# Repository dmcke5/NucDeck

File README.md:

# NucDeck
The Open Source DIY Handheld Gaming PC!

Refer to "NucDeck Assembly Instructions.PDF" for mechanical assembly details. Information for the electronics will be added once the controller PCB's are complete.

There are two different versions of the housing, Standard and NoRGB. The NoRGB version has had
the RGB joystick surrounds removed to simplify printing. If you choose the NoRGB version you can leave all of the 
associated components off the PCB's to save on cost.

There are two different versions of the buttons, membrane and clicky. The Membrane buttons are shorter and are
designed to be used with silicone membranes. I've included files for molds to make the membranes. If you have a resin printer
I encourage you to give this a try as it improves the feel of the buttons dramatically. FDM printers will struggle to produce the accuracy required to make these parts. The clicky version is slightly taller and can be used without the membranes.

Total Cost of parts approximately: $311 USD

This is based on PCBway's pricing for the PCB's and is not including a NUC or any shipping charges. I've probably missed counting something so I would budget for a little more!

Here's a breakdown of the costs:
- Digikey parts: $55 USD
- PCB's (Set of 5 due to MOQ): $204 USD
- Aliexpress Parts: $52 USD

If you can organise a group of 5 people who want a set of PCB's, you will greatly reduce your total cost to build.

#### Project Status
- [x] 3D Files
- [x] Software: V1.0 ready for testing. Motion controls not yet implemented
- [x] PCBs: Complete

Watch the series on Youtube as I design, build and test parts of this project:
- [Episode 1](https://youtu.be/xVYYCx3Qt4Y)
- [Episode 2](https://youtu.be/nOXd3axX4fw)
- [Episode 3](https://youtu.be/yHMnScoKIOE)
- [Episode 4](https://youtu.be/rP_sMztufNs)
- [Episode 5](https://youtu.be/sQocfy4pwIQ)
- [Bonus Episode - Battery Life Testing](https://youtu.be/6FQKwnMxRxI)
- [Episode 6](https://youtu.be/mfuAvgmuT2s)
- [Episode 7](https://youtu.be/nFNw7_WkteA)
- [Episode 8](https://youtu.be/YYRD0Zlga5s)
- [Episode 9](https://youtu.be/t9Rao_BeIeM)

I've found links for all of the parts on Aliexpress since its probably the cheapest option and will ship worldwide.

## Parts List

#### Display

Any 1024x600 50 Pin RGB Panel with overall dimensions no greater than 164.9x100x3.3mm.
This is the 700nit IPS panel I ended up using: https://www.aliexpress.com/item/1005005315348504.html

#### Display Driver

Pick the "PCB800812V1" option:
https://www.aliexpress.com/item/1005004252996145.html

#### USB Touch Controller

Pick option "USB Controller":
https://www.aliexpress.com/item/32976239800.html

#### Capacitive Touch Panel

This is the seller I used, but anyone selling for the same model tablet (Pritom K7) should do:
https://www.aliexpress.com/item/1005002490383977.html

#### Joysticks

Joysticks are an Alps RKJX21224001. Here's a cheap seller on aliexpress:
https://www.aliexpress.com/item/1005005264696228.html
Joystick caps are Xbox One compatible.

#### Batteries

4x 605080 3000mah Lithium cells. Here's a cheap supplier on Aliexpress:
https://www.aliexpress.com/item/32990176071.html

#### Info Screen

0.96" IPS 80x160 ST7735 TFT Display

You need the one these guys refer to as "Spliced Type".
https://www.aliexpress.com/item/1005001598020071.html

#### Threaded Inserts

Measurments are: Thread x OD x Length

17x M2x3.2x4

10x M3x5x5

2x M3x5x4

https://www.aliexpress.com/item/1005003582355741.html

#### Standoffs

10x M2x6mm Male to Female Standoffs
https://www.aliexpress.com/item/4001271908929.html

#### Trigger Springs

--NOTE-- Ignore the wire thickness in the Assembly Drawing, it is incorrect. I will fix it when I next need to make changes. Correct thickness listed here.
These guys have a lot of different options, they are pretty cheap so I'd grab a few different wire thicknesses
and test them out to see what you like. You need about 2mm ID on the coil section, so look for an ID of at least double the wire
thickness greater than 2mm. I found 0.4mm to feel a bit too thin, and 0.7mm is about the limit of the trigger supports so 0.5-0.6mm is probably the sweet spot.
https://www.aliexpress.com/item/1005004968066601.html

#### Trigger Magnets

You'll never need fridge magnets again!
https://www.aliexpress.com/item/1005003794726533.html

#### RGB Lights

You'll need both RGB LED's and WS2811 IC's if you're adding RGB to your controller PCB's.
These are the LED's I used. Any alternative in the same sized package should be fine too, just be cautious of
differing pin configurations.
https://www.aliexpress.com/item/1005003719602946.html

WS2811 IC's:
https://www.aliexpress.com/item/32844615804.html

#### Screws

Here's a list of the screws required for assembly. This list is also in the assembly instructions. SCHS is just a standard allen key head screw. CSK is a countersunk head screw. Most bolt suppliers should have these, otherwise ebay or aliexpress is your friend.

12x M3x6mm SHCS
2x M2x16 CSK
9x M2x5 CSK
14x M2x4 SHCS

#### 4s Cell Balancer
https://www.aliexpress.com/item/1005005827876691.html

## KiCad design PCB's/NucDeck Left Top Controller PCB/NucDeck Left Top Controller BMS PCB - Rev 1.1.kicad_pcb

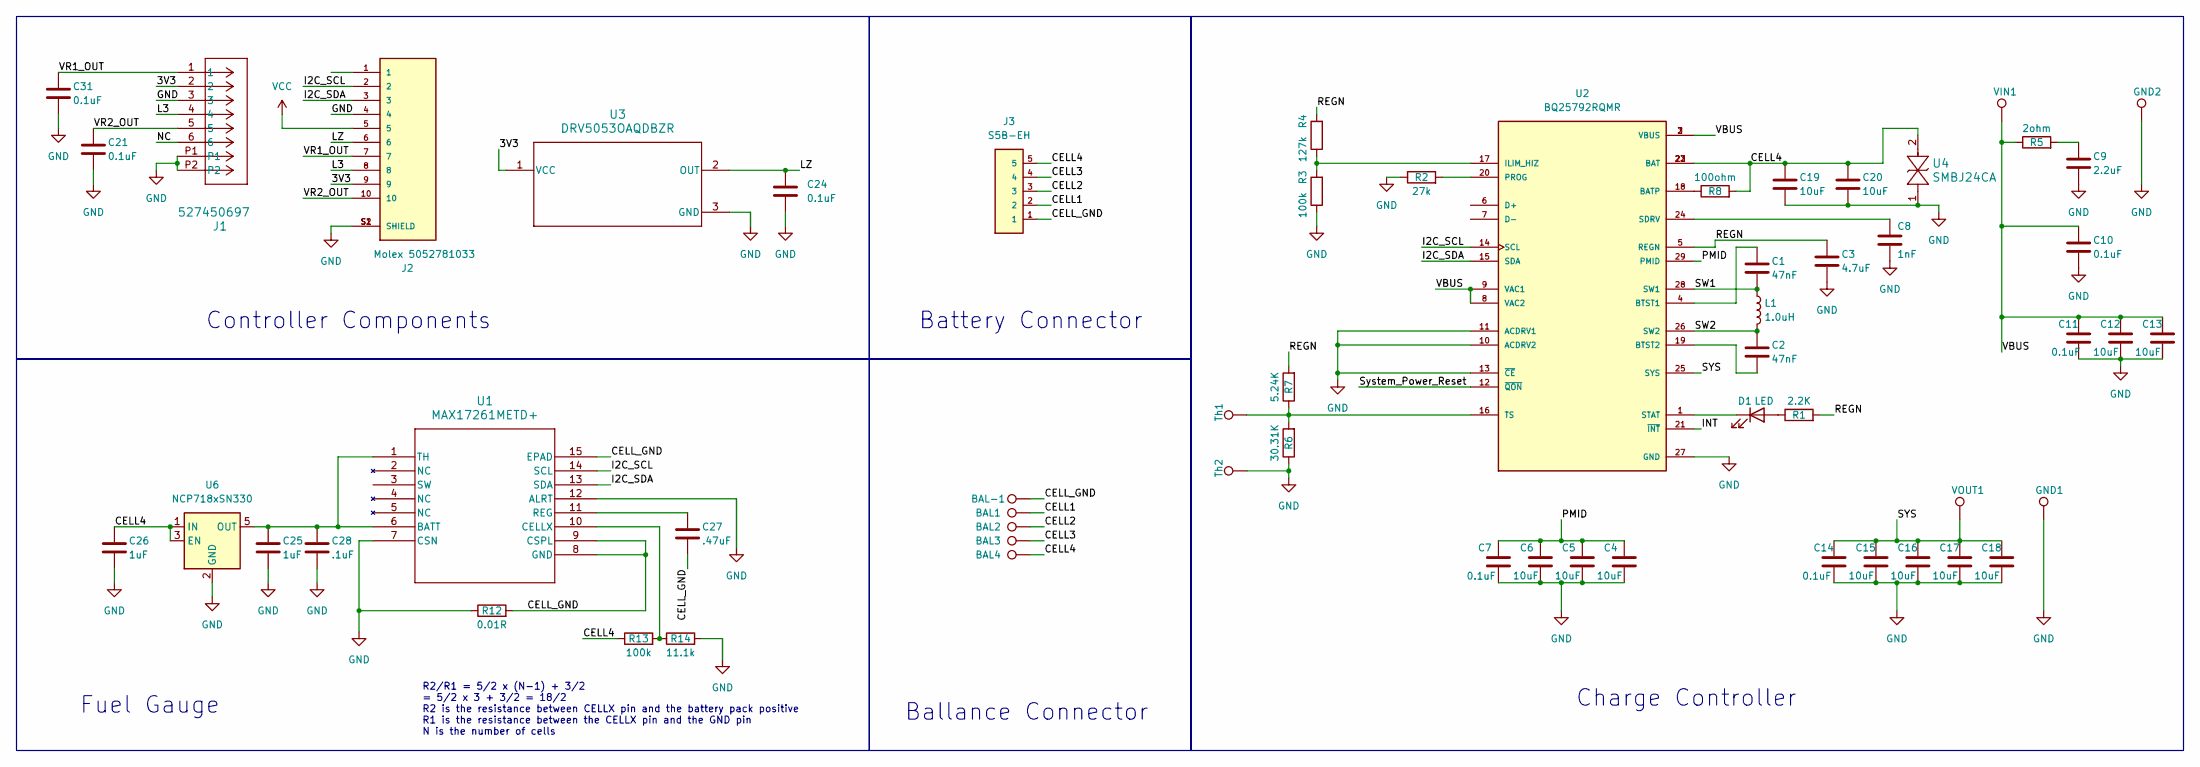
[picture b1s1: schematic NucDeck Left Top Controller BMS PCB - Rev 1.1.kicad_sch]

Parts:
BAL1, BAL2, BAL3, BAL4: TestPoint; TestPoint_Pad_1.0x1.0mm
BAL-1: TestPoint; TestPoint_Pad_1.0x1.0mm
C1, C2: 47nF; C_0603_1608Metric
C3: 4.7uF; C_0603_1608Metric
C4, C5, C6, C12, C13, C15, C16, C17, C18: 10uF; C_0805_2012Metric
C7, C10, C11, C14, C21, C24, C31: 0.1uF; C_0603_1608Metric
C8: 1nF; C_0603_1608Metric
C9: 2.2uF; C_0603_1608Metric
C19, C20: 10uF; C_0603_1608Metric
C25, C26: 1uF; C_0603_1608Metric
C27: .47uF; C_0603_1608Metric
C28: .1uF; C_0603_1608Metric
D1: LED; LED_0603_1608Metric
GND1, GND2: TestPoint; TestPoint_THTPad_D2.0mm_Drill1.0mm
J1: 527450697; CON_527450697_MOL
J2: Molex 5052781033; PARTREV A
J3: S5B-EH; JST_EH_S5B-EH_1x05_P2.50mm_Horizontal
L1: 1.0uH; IND_SPM6530_TDK
R1: 2.2K; R_0603_1608Metric
R2: 27k; R_0603_1608Metric
R3, R13: 100k; R_0603_1608Metric
R4: 127k; R_0603_1608Metric
R5: 2ohm; R_0603_1608Metric
R6: 30.31K; R_0603_1608Metric
R7: 5.24K; R_0603_1608Metric
R8: 100ohm; R_0603_1608Metric
R12: 0.01R; R_2512_6332Metric
R14: 11.1k; R_0603_1608Metric
Th1, Th2: 10K; TestPoint_THTPad_D1.0mm_Drill0.5mm
U1: MAX17261METD+; 21-0137_T1433+2C_MXM
U2: BQ25792RQMR; QFN40P400X400X100-29N; PARTREV 11/2019
U3: DRV5053OAQDBZR; DBZ0003A_N
U4: SMBJ24CA; SMBJ24CA_LTF
U6: NCP718xSN330; SOT-23-5
VIN1: TestPoint; TestPoint_THTPad_D2.0mm_Drill1.0mm
VOUT1: TestPoint; TestPoint_THTPad_D2.0mm_Drill1.0mm

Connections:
/3V3: J1.2, J2.9, U3.1 (VCC)
/CELL1: BAL1.1, J3.2
/CELL2: BAL2.1, J3.3
/CELL3: BAL3.1, J3.4
/CELL4: BAL4.1, C19.1, C20.1, C26.1, J3.5, R8.2, R13.1, U2.22 (BAT), U2.23 (BAT), U4.2, U6.1 (IN), U6.3 (EN)
/CELL_GND: BAL-1.1, C27.2, J3.1, R12.2, U1.8 (GND), U1.9 (CSPL), U1.15 (EPAD)
/I2C_SCL: J2.2, U1.14 (SCL), U2.14 (SCL)
/I2C_SDA: J2.3, U1.13 (SDA), U2.15 (SDA)
/INT: U2.21 (~INT)
/L3: J1.4, J2.8
/LZ: C24.1, J2.6, U3.2 (OUT)
/NC: J1.6
/PMID: C4.1, C5.1, C6.1, C7.1, U2.29 (PMID)
/REGN: C3.1, R1.2, R4.2, R7.2, U2.5 (REGN)
/SW1: C1.2, L1.1, U2.28 (SW1)
/SW2: C2.1, L1.2, U2.26 (SW2)
/SYS: C14.1, C15.1, C16.1, C17.1, C18.1, U2.25 (SYS), VOUT1.1; also elsewhere on the board
/System_Power_Reset: U2.12 (~QON)
/VBUS: C10.1, C11.1, C12.1, C13.1, R5.1, U2.2 (VBUS), U2.3 (VBUS), U2.8 (VAC2), U2.9 (VAC1), VIN1.1; also elsewhere on the board
/VR1_OUT: C31.1, J1.1, J2.7
/VR2_OUT: C21.1, J1.5, J2.10
GND: C3.2, C4.2, C5.2, C6.2, C7.2, C8.2, C9.2, C10.2, C11.2, C12.2, C13.2, C14.2, C15.2, C16.2, C17.2, C18.2, C19.2, C20.2, C21.2, C24.2, C25.2, C26.2, C28.2, C31.2, GND1.1, GND2.1, J1.3, J1.P1, J1.P2, J2.4, J2.11, J2.12, J2.S1 (SHIELD), J2.S2 (SHIELD), R2.1, R3.1, R6.1, R12.1, R14.2, Th2.1, U1.7 (CSN), U1.12 (ALRT), U2.10 (ACDRV2), U2.11 (ACDRV1), U2.13 (~CE), U2.27 (GND), U3.3 (GND), U4.1, U6.2 (GND); also elsewhere on the board
unnamed: C9.1, R5.2
unnamed: D1.2 (A), R1.1
unnamed: D1.1 (K), U2.1 (STAT)
unnamed: C25.1, C28.1, U1.1 (TH), U1.6 (BATT), U6.5 (OUT)
unnamed: R13.2, R14.1, U1.10 (CELLX)
unnamed: C27.1, U1.11 (REG)
unnamed: R8.1, U2.18 (BATP)
unnamed: C1.1, U2.4 (BTST1)
unnamed: C2.2, U2.19 (BTST2)
unnamed: R3.2, R4.1, U2.17 (ILIM_HIZ)
unnamed: R2.2, U2.20 (PROG)
unnamed: C8.1, U2.24 (SDRV)
unnamed: R6.2, R7.1, Th1.1, U2.16 (TS)
VCC: J2.5

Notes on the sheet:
Ballance Connector
Controller Components
Fuel Gauge
R2/R1 = 5/2 x (N-1) + 3/2 = 5/2 x 3 + 3/2 = 18/2 R2 is the resistance between CELLX pin and the battery pack positive R1 is the resistance between the CELLX pin and the GND pin N is the number of cells
Battery Connector
Charge Controller

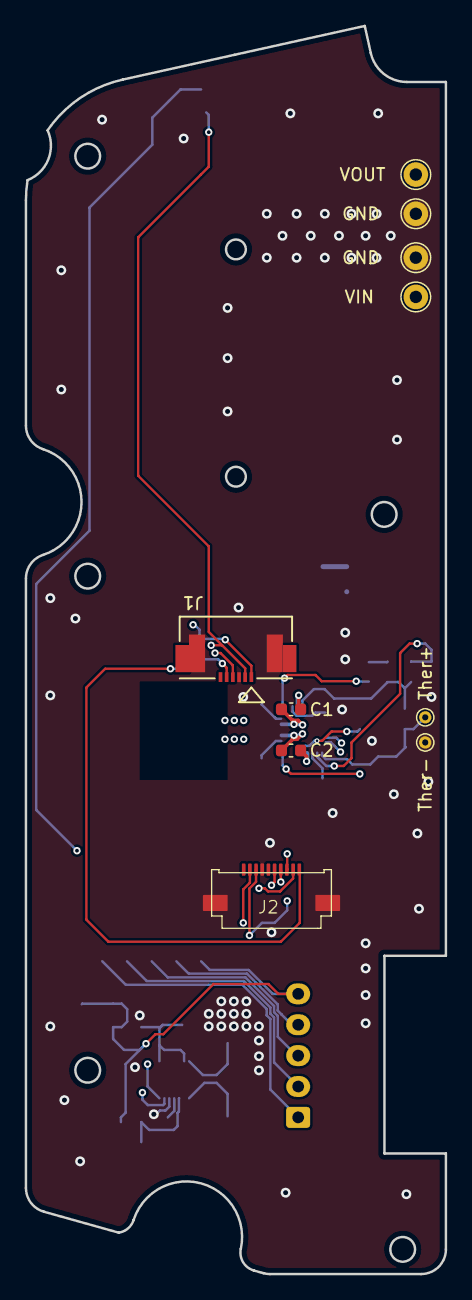
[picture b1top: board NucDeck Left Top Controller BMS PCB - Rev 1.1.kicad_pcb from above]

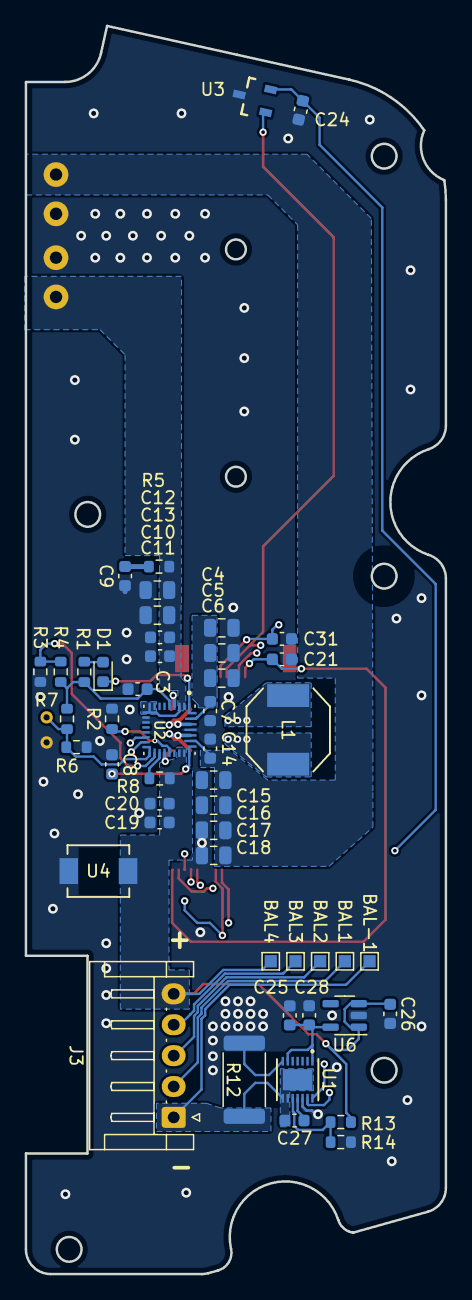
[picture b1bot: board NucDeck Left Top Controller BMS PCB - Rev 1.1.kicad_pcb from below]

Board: 4 copper layers, 34.0 x 101.0 mm, 59 parts (49 on the bottom side), 32 nets.

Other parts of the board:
GND: TestPoint; TestPoint_THTPad_D2.0mm_Drill1.0mm
GND#2: TestPoint; TestPoint_THTPad_D2.0mm_Drill1.0mm
VIN: TestPoint; TestPoint_THTPad_D2.0mm_Drill1.0mm
VOUT: TestPoint; TestPoint_THTPad_D2.0mm_Drill1.0mm

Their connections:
/SYS: VOUT.1; also elsewhere on the board
/VBUS: VIN.1; also elsewhere on the board
GND: GND.1, GND#2.1; also elsewhere on the board

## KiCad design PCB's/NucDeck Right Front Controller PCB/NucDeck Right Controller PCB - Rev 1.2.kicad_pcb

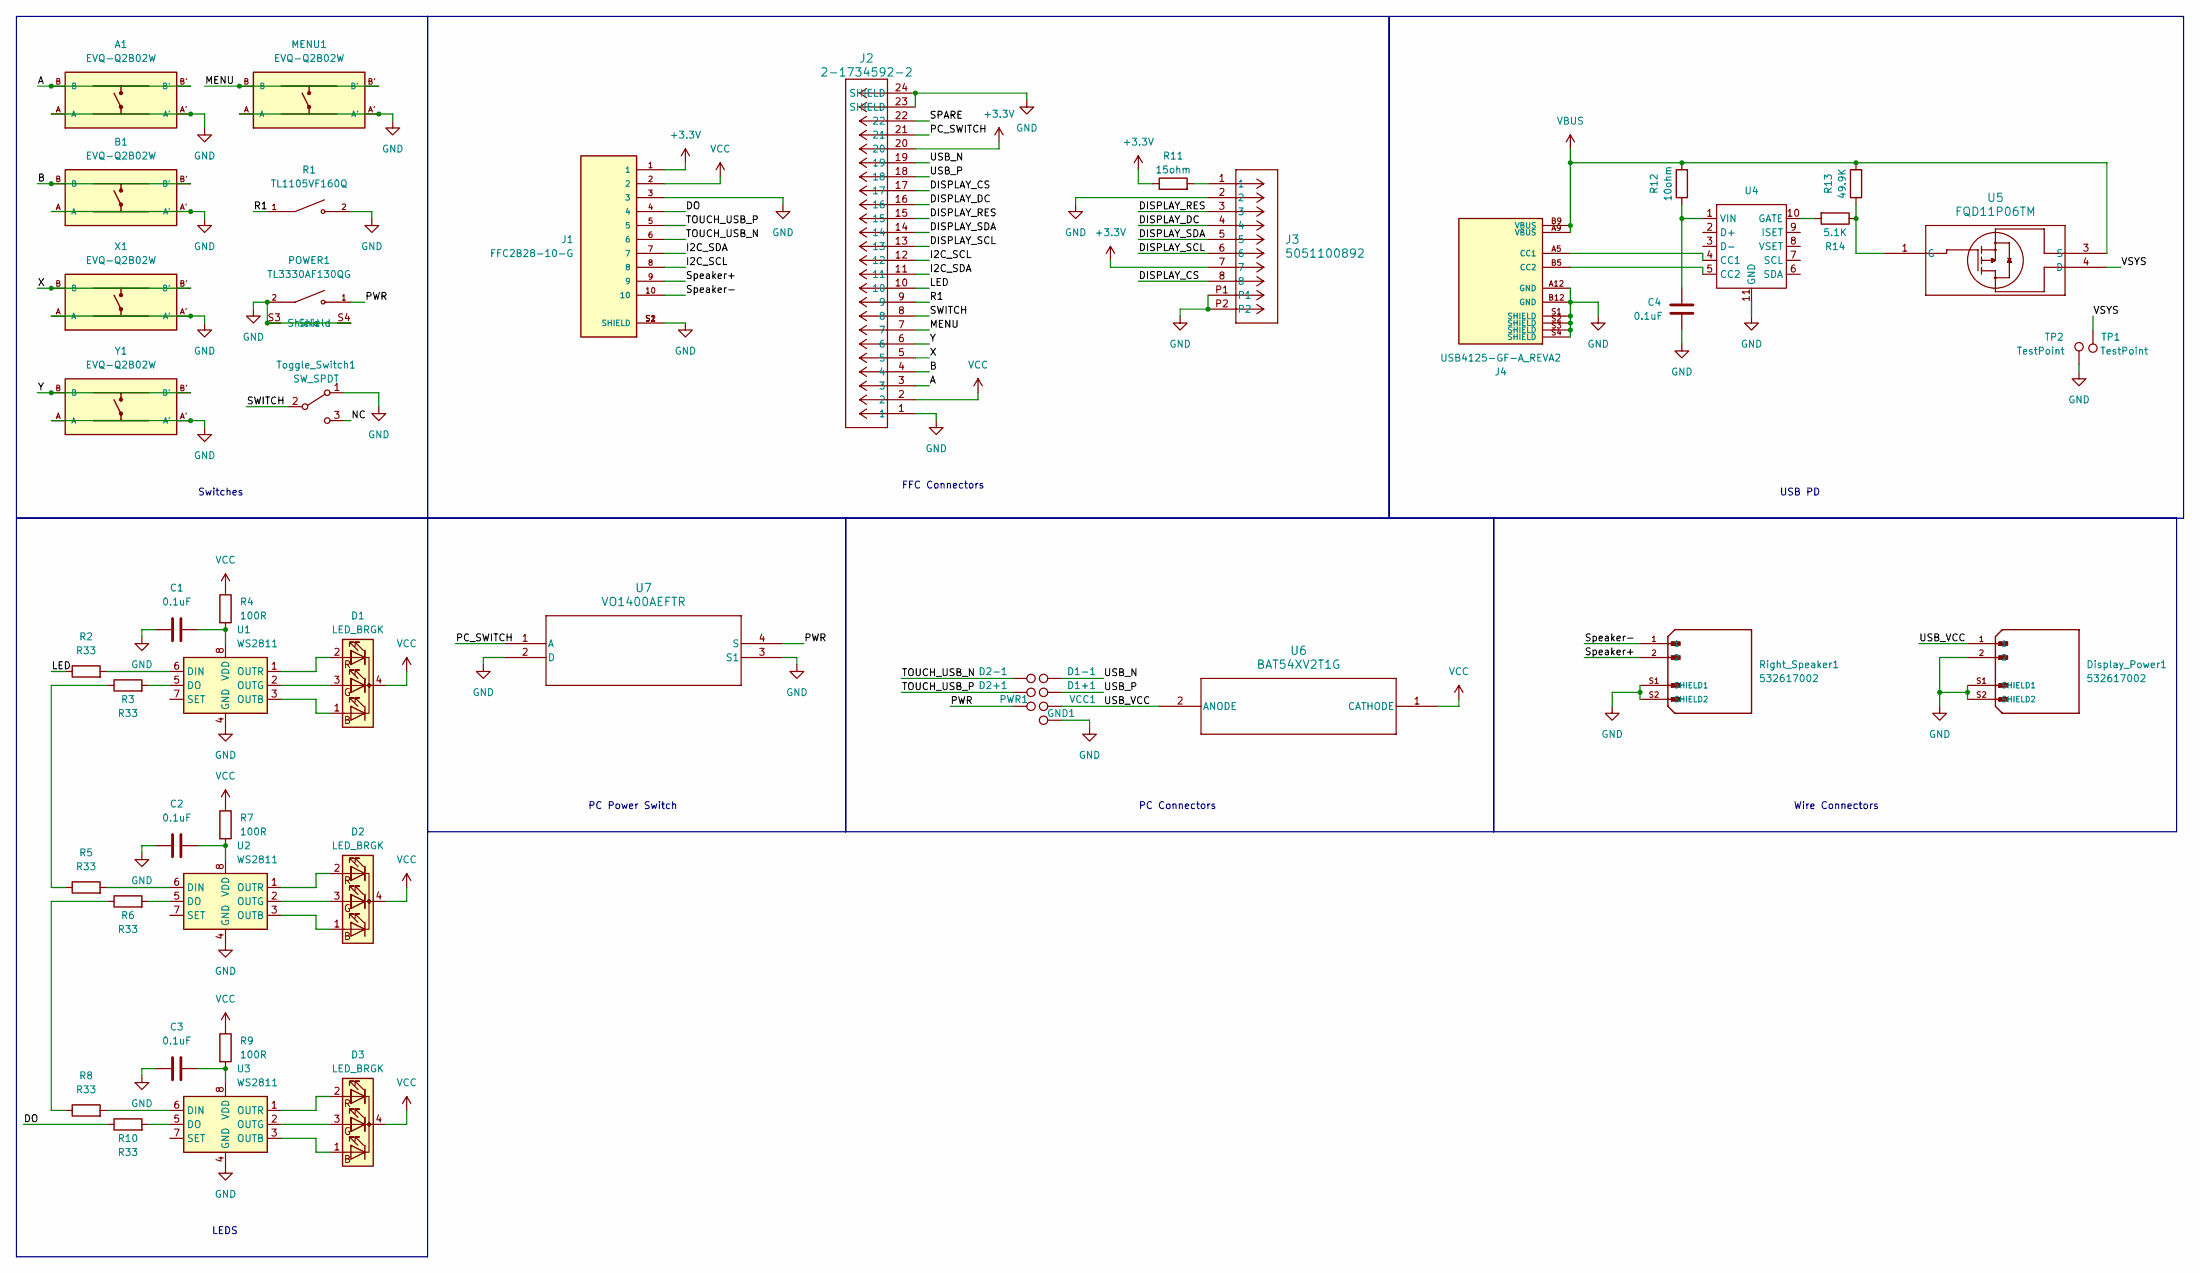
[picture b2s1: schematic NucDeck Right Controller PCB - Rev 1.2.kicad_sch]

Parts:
A1: EVQ-Q2B02W; SW_EVQ-Q2B02W
B1: EVQ-Q2B02W; SW_EVQ-Q2B02W
C1, C2, C3, C4: 0.1uF; C_0603_1608Metric_Pad1.08x0.95mm_HandSolder
D1, D2, D3: LED_BRGK; LED_T36K3BGR-05D000121U1930
D1+1, D1-1, D2+1, D2-1: TestPoint; TestPoint_THTPad_D1.0mm_Drill0.5mm
Display_Power1: 532617002; MOLEX_532617002; PARTREV B; DigiKey_Part_Number WM25389TR-ND
GND1: TestPoint; TestPoint_THTPad_D1.0mm_Drill0.5mm
J1: FFC2B28-10-G; Molex 5052781033; PARTREV A
J2: 2-1734592-2; CONN22_2-1734592-2
J3: 5051100892; CON_5051100892_MOL
J4: USB4125-GF-A_REVA2; GCT_USB4125-GF-A_REVA2; PARTREV Rev A2; DigiKey_Part_Number 2073-USB4125-GF-ATR-ND
MENU1: EVQ-Q2B02W; SW_EVQ-Q2B02W
POWER1: TL3330AF130QG; SW_TL3330AF130QG; PARTREV B
PWR1: TestPoint; TestPoint_THTPad_D1.0mm_Drill0.5mm
R1: TL1105VF160Q; SW_TL1105VF160Q; PARTREV C
R2, R3, R5, R6, R8, R10: R33; R_0603_1608Metric_Pad0.98x0.95mm_HandSolder
R4, R7, R9: 100R; R_0603_1608Metric_Pad0.98x0.95mm_HandSolder
R11: 15ohm; R_0603_1608Metric_Pad0.98x0.95mm_HandSolder
R12: 10ohm; R_0603_1608Metric_Pad0.98x0.95mm_HandSolder
R13: 49.9K; R_0603_1608Metric_Pad0.98x0.95mm_HandSolder
R14: 5.1K; R_0603_1608Metric_Pad0.98x0.95mm_HandSolder
Right_Speaker1: 532617002; MOLEX_532617002; PARTREV B; DigiKey_Part_Number WM25389TR-ND
TP1, TP2: TestPoint; TestPoint_THTPad_D1.5mm_Drill0.7mm
Toggle_Switch1: SW_SPDT; NKK SS12SBP2
U1, U2, U3: WS2811; SOP-8_3.9x4.9mm_P1.27mm
U4: DFN-10-1EP_3x3mm_P0.5mm_EP1.7x2.5mm
U5: FQD11P06TM; TO-252-3_ONS
U6: BAT54XV2T1G; SOD-523_0P9X1P3_ONS
U7: VO1400AEFTR; SO-4_VO_VIS
VCC1: TestPoint; TestPoint_THTPad_D1.0mm_Drill0.5mm
X1: EVQ-Q2B02W; SW_EVQ-Q2B02W
Y1: EVQ-Q2B02W; SW_EVQ-Q2B02W

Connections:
+3.3V: J1.1, J2.20, J3.7, R11.1
/A: A1.B, A1.B', J2.3
/B: B1.B, B1.B', J2.4
/DISPLAY_CS: J2.17, J3.8
/DISPLAY_DC: J2.16, J3.4
/DISPLAY_RES: J2.15, J3.3
/DISPLAY_SCL: J2.13, J3.6
/DISPLAY_SDA: J2.14, J3.5
/DO: J1.4, R10.1
/I2C_SCL: J1.8, J2.12
/I2C_SDA: J1.7, J2.11
/LED: J2.10, R2.1
/MENU: J2.7, MENU1.B, MENU1.B'
/NC: Toggle_Switch1.3 (C)
/PC_SWITCH: J2.21, U7.1 (A)
/PWR: POWER1.1, PWR1.1, U7.4 (S)
/R1: J2.9, R1.1
/SPARE: J2.22
/SWITCH: J2.8, Toggle_Switch1.2 (B)
/Speaker+: J1.9, Right_Speaker1.2
/Speaker-: J1.10, Right_Speaker1.1
/TOUCH_USB_N: D2-1.1, J1.6
/TOUCH_USB_P: D2+1.1, J1.5
/USB_N: D1-1.1, J2.19
/USB_P: D1+1.1, J2.18
/USB_VCC: Display_Power1.1, U6.2 (ANODE), VCC1.1
/VSYS: TP1.1, U5.4 (D)
/X: J2.5, X1.B, X1.B'
/Y: J2.6, Y1.B, Y1.B'
GND: A1.A, A1.A', B1.A, B1.A', C1.1, C2.1, C3.1, C4.2, Display_Power1.2, Display_Power1.S1 (SHIELD1), Display_Power1.S2 (SHIELD2), GND1.1, J1.3, J1.11, J1.12, J1.S1 (SHIELD), J1.S2 (SHIELD), J2.1, J2.23 (SHIELD), J2.24 (SHIELD), J3.2, J3.P1, J3.P2, J4.1, J4.2, J4.3, J4.4, J4.A12 (GND), J4.B12 (GND), J4.S1 (SHIELD), J4.S2 (SHIELD), J4.S3 (SHIELD), J4.S4 (SHIELD), MENU1.A, MENU1.A', POWER1.2, POWER1.S1, POWER1.S3 (Shield), POWER1.S4 (Shield), R1.2, R1.S1, R1.S2, Right_Speaker1.S1 (SHIELD1), Right_Speaker1.S2 (SHIELD2), TP2.1, Toggle_Switch1.1 (A), U1.4 (GND), U2.4 (GND), U3.4 (GND), U4.11 (GND), U7.2 (D), U7.3 (S1), X1.A, X1.A', Y1.A, Y1.A'
unnamed: D1.1 (BA), U1.3 (OUTB)
unnamed: D1.3 (GA), U1.2 (OUTG)
unnamed: D1.2 (RA), U1.1 (OUTR)
unnamed: D2.1 (BA), U2.3 (OUTB)
unnamed: D2.3 (GA), U2.2 (OUTG)
unnamed: D2.2 (RA), U2.1 (OUTR)
unnamed: D3.1 (BA), U3.3 (OUTB)
unnamed: D3.3 (GA), U3.2 (OUTG)
unnamed: D3.2 (RA), U3.1 (OUTR)
unnamed: J3.1, R11.2
unnamed: J4.A5 (CC1), U4.4 (CC1)
unnamed: J4.B5 (CC2), U4.5 (CC2)
unnamed: R3.1, R5.1
unnamed: R6.1, R8.1
unnamed: R2.2, U1.6 (DIN)
unnamed: R3.2, U1.5 (DO)
unnamed: C1.2, R4.2, U1.8 (VDD)
unnamed: R5.2, U2.6 (DIN)
unnamed: R6.2, U2.5 (DO)
unnamed: C2.2, R7.2, U2.8 (VDD)
unnamed: R8.2, U3.6 (DIN)
unnamed: R10.2, U3.5 (DO)
unnamed: C3.2, R9.2, U3.8 (VDD)
unnamed: R14.2, U4.10 (GATE)
unnamed: C4.1, R12.1, U4.1 (VIN)
unnamed: R13.1, R14.1, U5.1 (G)
VBUS: J4.A9 (VBUS), J4.B9 (VBUS), R12.2, R13.2, U5.3 (S)
VCC: D1.4 (K), D2.4 (K), D3.4 (K), J1.2, J2.2, R4.1, R7.1, R9.1, U6.1 (CATHODE)

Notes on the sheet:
Switches
PC Power Switch
PC Connectors
FFC Connectors
LEDS
USB PD
Wire Connectors

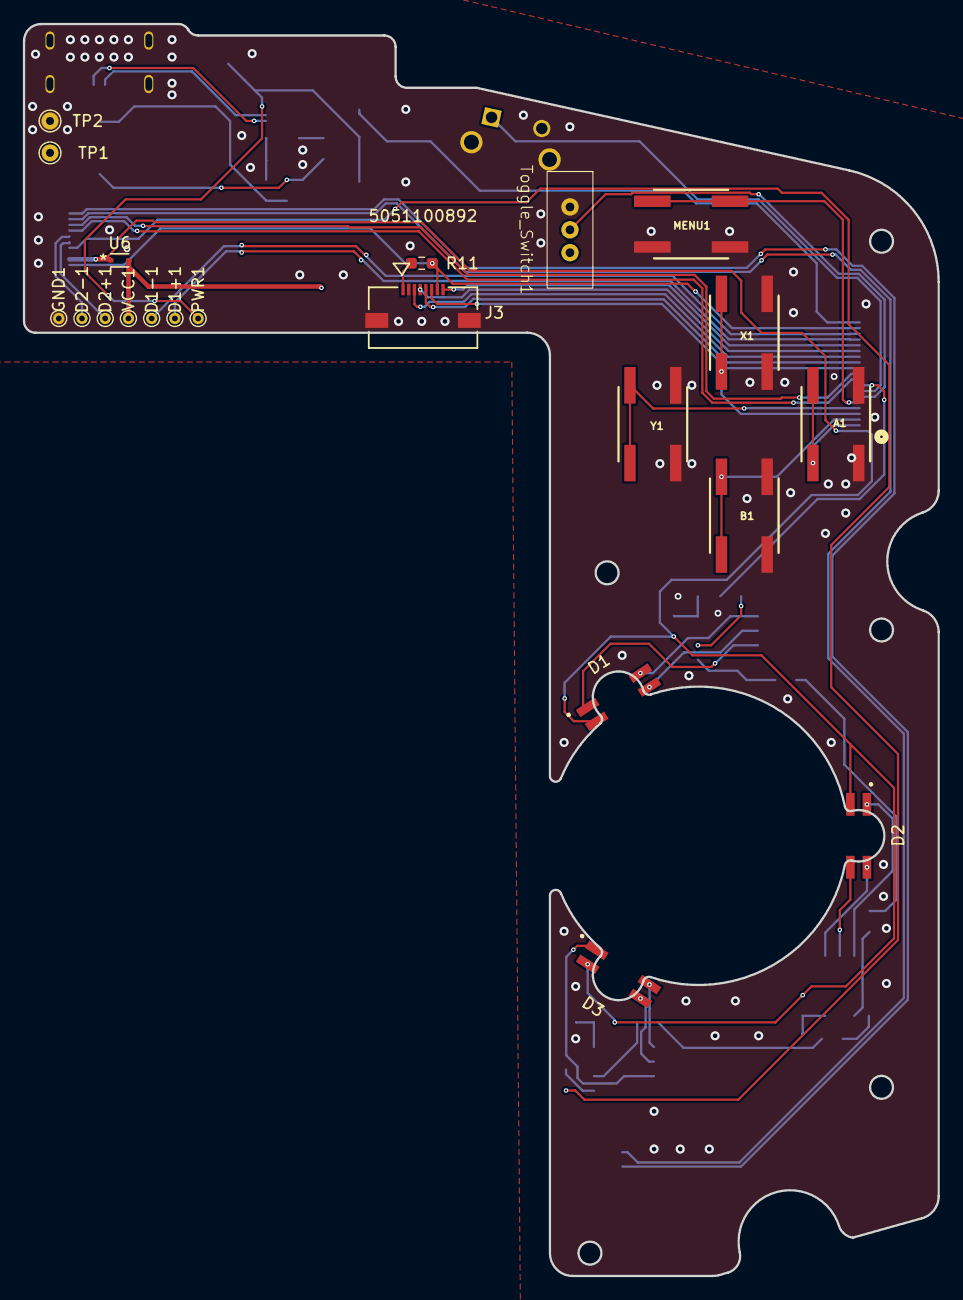
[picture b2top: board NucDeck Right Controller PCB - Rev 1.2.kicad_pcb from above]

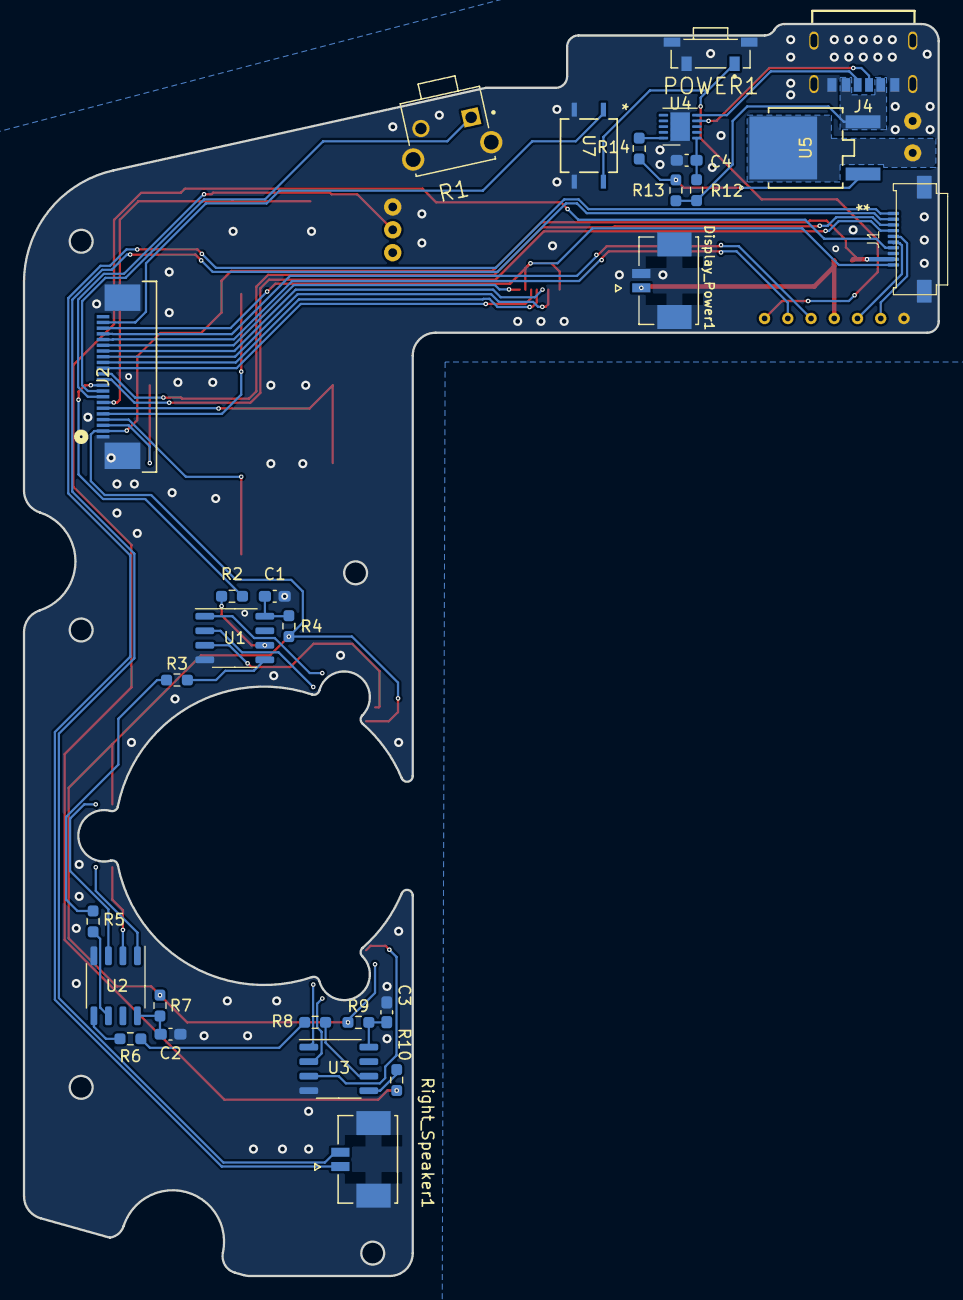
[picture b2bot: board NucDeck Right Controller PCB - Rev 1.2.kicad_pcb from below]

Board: 2 copper layers, 80.0 x 109.5 mm, 50 parts (29 on the bottom side), 56 nets.

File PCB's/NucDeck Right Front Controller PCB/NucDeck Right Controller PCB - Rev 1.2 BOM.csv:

All parts available from Digikey unless otherwise specified,,,,
,,,,
Ref,Qnty,Value/Part Number,Footprint,Supplier
"A1,B1,X1,Y1,MENU1",5,EVQ-Q2B02W,SW_EVQ-Q2B02W,
"C1, C2, C3, C4",4,0.1uF,Capacitor 0603_1608Metric,
"D1, D2, D3",3,LED_BRGK,LED_SMD:LED_T36K3BGR-05D000121U1930,https://www.aliexpress.com/item/1005003719602946.html
Display_Power1,1,532617002,MOLEX_532617002,
J1,1,5052781033,Molex Easy On Connector:Molex 5052781033,
J2,1,2-1734592-2,CONN22_2-1734592-2,
J3,1,5051100892,CON_5051100892_MOL,
J4,1,USB4125-GF-A-0190,USB4125-GF-A-0190,
POWER1,1,TL3330AF130QG,SW_TL3330AF130QG,
R1,1,TL1105VF160Q,SW_TL1105VF160Q,
"R2, R3, R5, R6, R8, R10",6,R33,Resistor 0603_1608Metric,
"R4, R7, R9",3,100R,Resistor 0603_1608Metric,
R11,1,15ohm,Resistor 0603_1608Metric,
R12,1,10ohm,Resistor 0603_1608Metric,
R13,1,49.9K,Resistor 0603_1608Metric,
R14,1,5.1K,Resistor 0603_1608Metric,
Right_Speaker1,1,532617002,MOLEX_532617002,
Toggle_Switch1,1,SW_SPDT,NKK Slide Switch:NKK SS12SBP2,
"U1, U2, U3",3,WS2811,SOP-8_3.9x4.9mm_P1.27mm,https://www.aliexpress.com/item/32844615804.html
U4,1,HUSB238,DFN-10-1EP_3x3mm_P0.5mm_EP1.7x2.5mm,https://www.aliexpress.com/item/1005005555514096.html
U5,1,FQD11P06TM,TO-252-3_ONS,
U6,1,BAT54XV2T1G,SOD-523_0P9X1P3_ONS,
U7,1,VO1400AEFTR,SO-4_VO_VIS,

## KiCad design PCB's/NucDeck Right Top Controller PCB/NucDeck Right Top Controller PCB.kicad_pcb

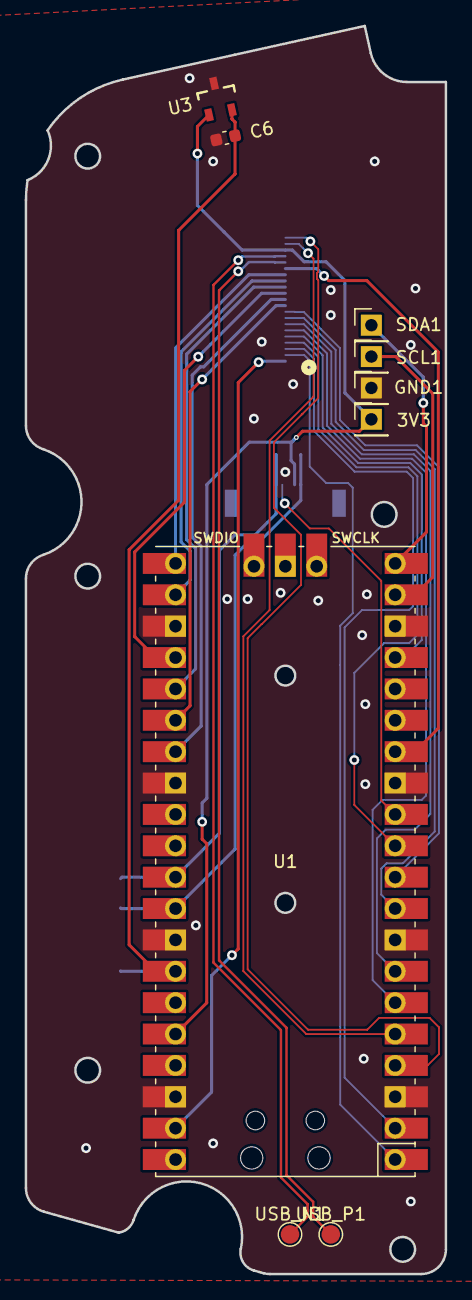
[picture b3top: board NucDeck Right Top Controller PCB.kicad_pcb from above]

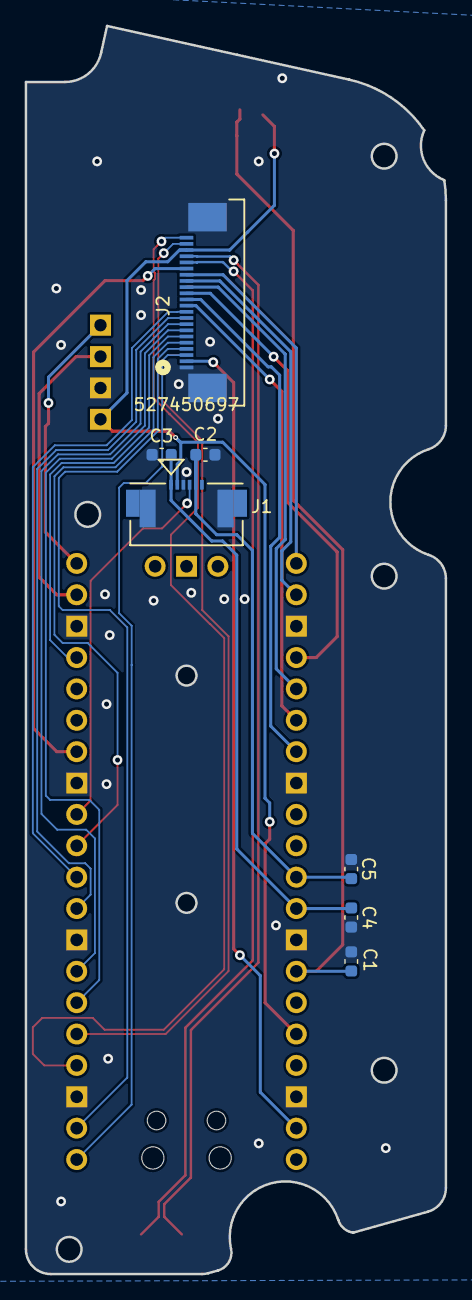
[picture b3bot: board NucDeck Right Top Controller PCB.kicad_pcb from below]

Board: 2 copper layers, 34.0 x 101.0 mm, 16 parts (7 on the bottom side), 28 nets.

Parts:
3V3: TestPoint; PinHeader_1x01_P2.54mm_Vertical
C1, C2, C3, C4, C5, C6: 0.1uF; C_0603_1608Metric
GND1: TestPoint; PinHeader_1x01_P2.54mm_Vertical
J1: 527450697; CON_527450697_MOL
J2: 2-1734592-2; CONN22_2-1734592-2
SCL1: TestPoint; PinHeader_1x01_P2.54mm_Vertical
SDA1: TestPoint; PinHeader_1x01_P2.54mm_Vertical
U1: Pico; RPi_Pico_SMD_TH
U3: DRV5053OAQDBZR; DBZ0003A_N
USB_N1: TestPoint; TestPoint_Pad_D1.5mm
USB_P1: TestPoint; TestPoint_Pad_D1.5mm

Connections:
+3.3V: 3V3.1, J1.2, J2.20, U1.36 (3V3), U3.1 (VCC)
/A: J2.3, U1.1 (GPIO0)
/B: J2.4, U1.2 (GPIO1)
/DISPLAY_CS: J2.17, U1.14 (GPIO10)
/DISPLAY_DC: J2.16, U1.21 (GPIO16)
/DISPLAY_RES: J2.15, U1.22 (GPIO17)
/DISPLAY_SCL: J2.13, U1.24 (GPIO18)
/DISPLAY_SDA: J2.14, U1.25 (GPIO19)
/I2C_SCL: J2.12, U1.27 (GPIO21)
/I2C_SDA: J2.11, U1.26 (GPIO20)
/LED: J2.10, U1.10 (GPIO7)
/MENU: J2.7, U1.6 (GPIO4)
/MPU6050_SCL: SDA1.1, U1.20 (GPIO15)
/MPU6050_SDA: SCL1.1, U1.19 (GPIO14)
/PC_SWITCH: J2.21, U1.5 (GPIO3)
/R1: J2.9, U1.9 (GPIO6)
/R3: J1.4, U1.12 (GPIO9)
/RZ: C1.1, C6.1, U1.34 (GPIO28_ADC2), U3.2 (OUT)
/SPARE: J2.22, U1.4 (GPIO2)
/SWITCH: J2.8, U1.7 (GPIO5)
/USB_N: J2.19, USB_N1.1
/USB_P: J2.18, USB_P1.1
/VR1_OUT: C3.1, C4.1, J1.1, U1.32 (GPIO27_ADC1)
/VR2_OUT: C2.1, C5.1, J1.5, U1.31 (GPIO26_ADC0)
/X: J2.5, U1.11 (GPIO8)
/Y: J2.6, U1.17 (GPIO13)
GND: C1.2, C2.2, C3.2, C4.2, C5.2, C6.2, GND1.1, J1.3, J1.P1, J1.P2, J2.1, J2.23 (SHIELD), J2.24 (SHIELD), U1.3 (GND), U1.8 (GND), U1.13 (GND), U1.18 (GND), U1.23 (GND), U1.28 (GND), U1.33 (AGND), U1.38 (GND), U3.3 (GND)
VCC: J2.2, U1.39 (VSYS)
